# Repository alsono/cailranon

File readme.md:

# introduction
This is an arduino nano powered hand held rail gun that runs on a 24V (12vx2) battery thats somewhat simple to use <br>
this took me more than it should have since i'm generally learning cad (around 9 hours) <br>
24v battery should be charged with crocodile clips as its hooked up via relay <br>
system works on a 5V battery on the side that must be removed before charging <br>
it has a cooldown of 5 seconds after every shot to avoid overheating the coils <br>
 <br>
# how to use
load it up like a musket with the metal pellets they use for slingshots, aim at your target and press the trigger, it should make a loud ass beep as it shoots <br>
# what to use this for?
- NOT killing people 
- shooting at soda cans
- killing tomatoes/ref
# how it works
think of it like a 3 step motor, the power cycles between 3 coils in the gun barrel infront of the projectile pulling it forward <br> 
and then cycling to the next one right away <br>
# warning i am not legally accounted with any harm caused from this outside its intended use or during malfunction
## tools you'll need
- soldering iron and solder
- superglue (bear with me)
- hot glue gun (bear with me here)
- acess to a 3d printer (you can use jlc3dp)
## parts you'll need
- check out the bom  (bill of materials)
- order the pcb from jlcpcb.com using the gerber.rar in production files
## how to build
## software
setup steps:
- download arduino ide
- download the file in railgunsoftware
- run it with arduino ide
- attach your arduino nano to your pc
- press the checkmark on the top left and wait for it flash
### printing
first set (or order) these parts to 3d print while you work on the hw:
- the main body with the cover <br>
 <br>
- the barrel (if your printer is too small you can split it into 2 and glue it together) <br>
 <br>
note: ideally you should print the barrel laying down so its way more sturdy and doesn't break off <br>
### soldering
solder the components so it looks like this (arduino nano on the bottom) <br>
 <br>
now solder a wire to each of these <br>
 <br>
run said wires through here <br>
 <br>
and then solder them to the switch like so <br>
 <br>
 next solder a 5v battery to the 5v pin on the nano (run the connection through here) <br>
  <br>
 and (bear with me) hot glue it to the side <br>
 next grab the 3 relays and wire them to these (relay part pointing down from it) <br>
.png) <br>
run the cable through these <br>
 <br>
and (bear with me) hot glue them here <br>
 <br>
grab 2 12V batteries and wire them in series and then wire them here (- is down + is up) and make sure the wire is long enough for you to carry them in a bag <br>
 <br>
last step: <br>
grab 3 of the longest copper wires you can find ideally 1.25mm and run the following equasion <br>

the more wire you have the better just don't over do it <br>
pass the 3 wires from the front through these two holes <br>
 <br>
solder said wires here <br>
 <br>
run [(your wire length) - 1612mm]/192.71786 on your calculator <br>
the number you get is the amount of turns each coil gets, hope you got a lot of wire!! <br>
do the amount of turns you got on these with the topmost wire you soldered to the diodes around these parts <br>
 <br>
drip down superglue onto each coil to both lock it in place and make sure it doesn't short out if the wax layer is burnt off due to usage <br>
now after running it back through the same hole solder it to this part <br>
 <br>
repeat the above 2 more times for the other 2 wires (don't put the coils on top of eachother i meant put wire 2 on every 3rd spot without wire already starting from the 2nd)
# qna
"why don't you hold stuff down with bolts?" gun explodes <br>
"whys there no relay module in the demonstrations?" i could not for the life of me find one and i've spent too much on this project to make one 
## stuff for nerds
the schematic used you can find it in pcb <br>
<br>
the pcb design wiring <br>
<br>
# demo links
- [onshape 3d model](https://cad.onshape.com/documents/b5d65689f200aad3e485e3da/w/5ed7d26aa7ff4d9a5b7cf364/e/11ed56f53a2aa773af70aec3)
- [pcb](https://kicanvas.org/?repo=https%3A%2F%2Fgithub.com%2Falsono%2Fcailranon%2Fblob%2Fmain%2Fpcb%2Frailgun.kicad_pro)

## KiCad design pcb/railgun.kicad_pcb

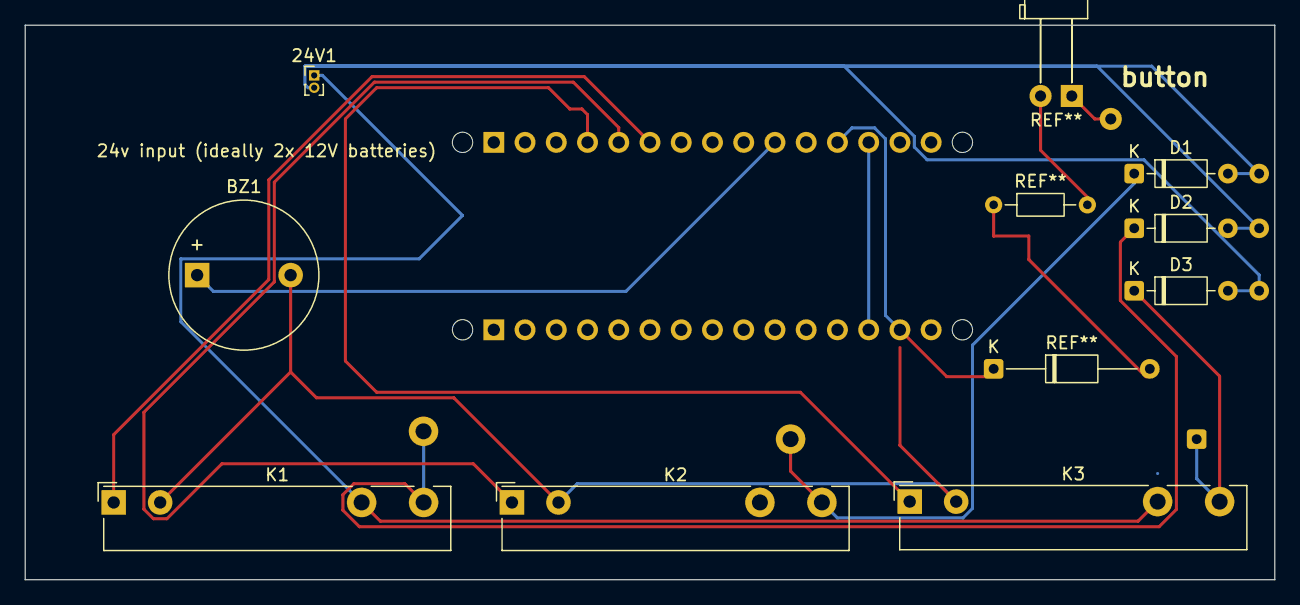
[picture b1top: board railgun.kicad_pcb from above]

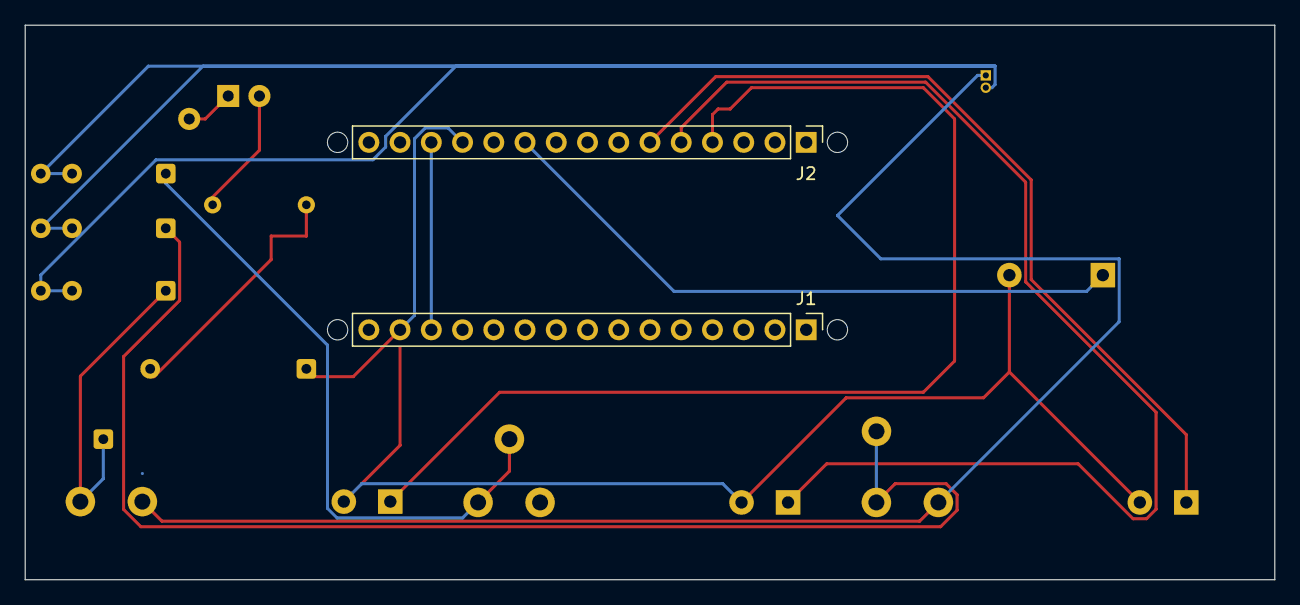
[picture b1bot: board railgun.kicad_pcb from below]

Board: 2 copper layers, 101.6 x 45.1 mm, 14 parts (2 on the bottom side), 11 nets.

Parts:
24V1: Battery; PinHeader_1x02_P1.00mm_Vertical
BZ1: Buzzer; Buzzer_12x9.5RM7.6
D1, D2, D3: 1N914; D_DO-35_SOD27_P7.62mm_Horizontal
J1: Analog; PinHeader_1x15_P2.54mm_Vertical
J2: Digital; PinHeader_1x15_P2.54mm_Vertical
K1, K2, K3: Fujitsu_FTR-LYAA005x; Relay_SPST-NO_Fujitsu_FTR-LYAA005x_FormA_Vertical
MH1, MH2, MH3, MH4: MountingHole_65mil

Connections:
/*D3: BZ1.1 (+), J2.10
/*D9: J2.4, K3.A1
/D7: J2.6, K1.A1
/D8: J2.5, K2.A1
/~RESET: J1.13, J2.13
GND: BZ1.2 (-), J1.14, J2.12, K1.A2, K2.A2, K3.A2
unnamed: 24V1.1 (+), K1.13, K3.13
unnamed: 24V1.2 (-), D1.2 (A), D2.2 (A), D3.2 (A)
unnamed: D1.1 (K), K2.14
unnamed: D2.1 (K), K1.14
unnamed: D3.1 (K), K3.14
